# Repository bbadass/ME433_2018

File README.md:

Bianca Baldassarri
04.05.18

Repository with homework from ME433, divided into folders by homework number

Have fun browsing!

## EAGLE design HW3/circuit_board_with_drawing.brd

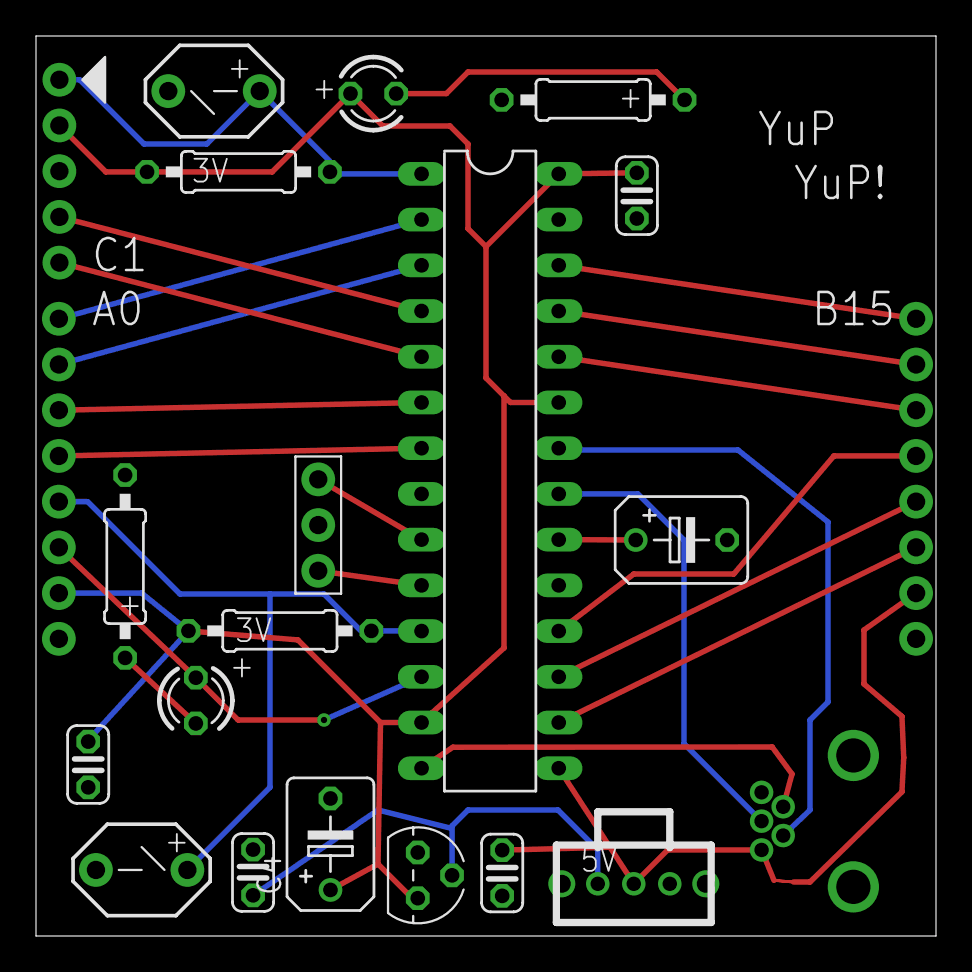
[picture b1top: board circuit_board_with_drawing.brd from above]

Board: 2 copper layers, 50.0 x 50.0 mm, 22 parts (0 on the bottom side), 27 nets.

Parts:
C1, C2, C3, C6: C025-024X044
C4, C5: B45181B
LED1, LED2: LED3MM
R1, R2, R3, R4: 0207/10
U$1: PIC32MX250F128B; DIL28-3
U$2, U$3: PUSH_BUTTON_SPST-NO; 1X03
U$4: USB_MINI; USB-MB-H
U$5: MCP1072; TO92
U$6: SLIDE_SWITCH; SLIDE_SW
U$7: OSC; 1X03
U$8: PICKIT; 1X05
U$9, U$10: CONNECTOR_8PIN-HOLES; 1X08

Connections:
+3V3: C2.1, C3.1, C4.+, LED1.A, R2.1, R3.1, U$1.13, U$1.23, U$1.28, U$5.3, U$8.2, U$10.7
+5V: C6.1, U$1.15, U$4.VBUS, U$6.2, U$9.2
GND: C1.2, C2.2, C3.2, C4.-, C5.-, C6.2, R1.2, R4.1, U$1.8, U$1.19, U$1.27, U$2.2, U$3.1, U$4.GND, U$5.1, U$7.2, U$8.3, U$9.1, U$10.8
unnamed: LED1.K, R1.1
unnamed: LED2.K, R4.2
unnamed: R2.2, U$1.1, U$2.1, U$8.1
unnamed: C5.+, U$1.20
unnamed: U$1.22, U$4.D-
unnamed: U$1.21, U$4.D+
unnamed: C1.1, U$5.2, U$6.1
unnamed: U$1.9, U$7.1
unnamed: U$1.10, U$7.3
unnamed: U$1.5, U$8.5
unnamed: U$1.4, U$8.4
RA0: U$1.2, U$10.1
RA1: U$1.3, U$10.2
RA4: LED2.A, U$1.12, U$10.6
RB2: U$1.6, U$10.3
RB3: U$1.7, U$10.4
RB4: R3.2, U$1.11, U$3.2, U$10.5
RB7: U$1.16, U$9.3
RB8: U$1.17, U$9.4
RB9: U$1.18, U$9.5
RB13: U$1.24, U$9.6
RB14: U$1.25, U$9.7
RB15: U$1.26, U$9.8
USB: U$1.14, U$4.ID

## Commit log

2018-04-05 Committing from terminal
2018-04-05 Starting HW1
2018-04-05 change file name
2018-04-05 remove old file
2018-04-09 Starting to write out circuit building steps
2018-04-09 Oscillation pictures
2018-04-09 Built circuit
2018-04-09 Adding picture of finished circuit
2018-04-09 Starting code
2018-04-09 Set the pragma values
2018-04-10 Set input and output pins
2018-04-10 Circui diagram
2018-04-10 Led on and off
2018-04-10 Led on and off, right this time
2018-04-10 Push button reset
2018-04-10 LED blinking piture
2018-04-10 Better circuit
2018-04-10 Starting to design circuit diagram
2018-04-10 First elements and connections
2018-04-11 Added PIC32
2018-04-13 Added USB
2018-04-14 Added slide switch
2018-04-16 Pushing all libraries
2018-04-16 One more
2018-04-16 Finished schematic
2018-04-17 Better schematic
2018-04-17 Put elements on board
2018-04-17 Small changes
2018-04-17 Schematic almost done, two connections not working
2018-04-17 Board fixed
2018-04-17 Added drawing at the back
2018-04-17 Adding Gerber files
2018-04-17 Slightly cjhanged image position
2018-04-18 Wired circuit
2018-04-19 circuit diagram added
2018-04-20 Voltages set to constant 1.65V adn 0.825V
2018-04-20 Channel B set to triangle wave
2018-04-20 Channel A set to sine wave
2018-04-20 Adding image
2018-04-20 Finished wireing cicruit
2018-04-20 Fixed crcuit
2018-04-21 code to turn secod led on finished, but led doen't turn on
2018-04-23 LED on and off when button is pressed
2018-04-23 video
2018-04-24 deleted initial delay in code
2018-04-24 started code
2018-04-24 everything works!
2018-04-24 Added video
2018-04-27 connection establishe: whoami works!
2018-04-28 reading of channels stil probably wrong but everything else should work
2018-04-30 everything worksgit add Biaca_Baldassarri_HW7.MOV note: y acceleration is negative upwards
2018-05-01 made the first code with the other ones
2018-05-01 more clear comments
2018-05-01 Started new HArmony code, blinking of LED with push button works!
2018-05-01 Code from HW7 added and works, note separation between what's inside the while loop and what not, and that initialisations of variables have to be inside same funciton where they are used
2018-05-03 code_o already in HW1
2018-05-03 note on difference in code for Harmony
2018-05-03 Windows sees now USB port, gonna program on virtual box and read on windows
2018-05-03 Black LCD and LED ON work, so initilaisation is good
2018-05-03 works now!
2018-05-03 Adding video
2018-05-08 MAF works
2018-05-09 All filters work, can optimize later
2018-05-09 Finished filters and testing for optimization, MAF 3 is best
2018-05-11 not exactly 3s to get across screen but works
2018-05-11 Changed code name
2018-05-15 everything works, did nothing fancy, might add stuff later for fun, don't really understand what android:test does yet
2018-05-17 everything works
2018-05-22 Board works, prints 100 numbers, 5 per second
2018-05-22 Seems to sort of work, but it appears as it capture characters only at times, it does store them in hte buffer though
2018-05-22 app works in the initial stage (no USB communication yet)
2018-05-22 conncetion with USB works for sending number from the PIC
2018-05-28 Picture of the wheel (don't know how to save it
2018-05-29 Box drawn
2018-05-29 Adding dwg files
2018-05-29 Files to print added
2018-06-08 App works decently under most light conditions, maybe if the camera could be distanced it would be better
2018-06-10 App should mabe work, but missing PI code for PIC
2018-06-10 Still does not work and miss PI
2018-06-11 Motor control seems to work
2018-06-12 The basic work, can follow a straight line but turning it's still a problem, now going to delete a bunch of stuff being printed to the screen in android
2018-06-14 Adding video and latest version of code: robot works if it goes slow enough, but cannot go that slow without being pushed fairly frequently because it's heavy and single wheel motion sometimes cannot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
